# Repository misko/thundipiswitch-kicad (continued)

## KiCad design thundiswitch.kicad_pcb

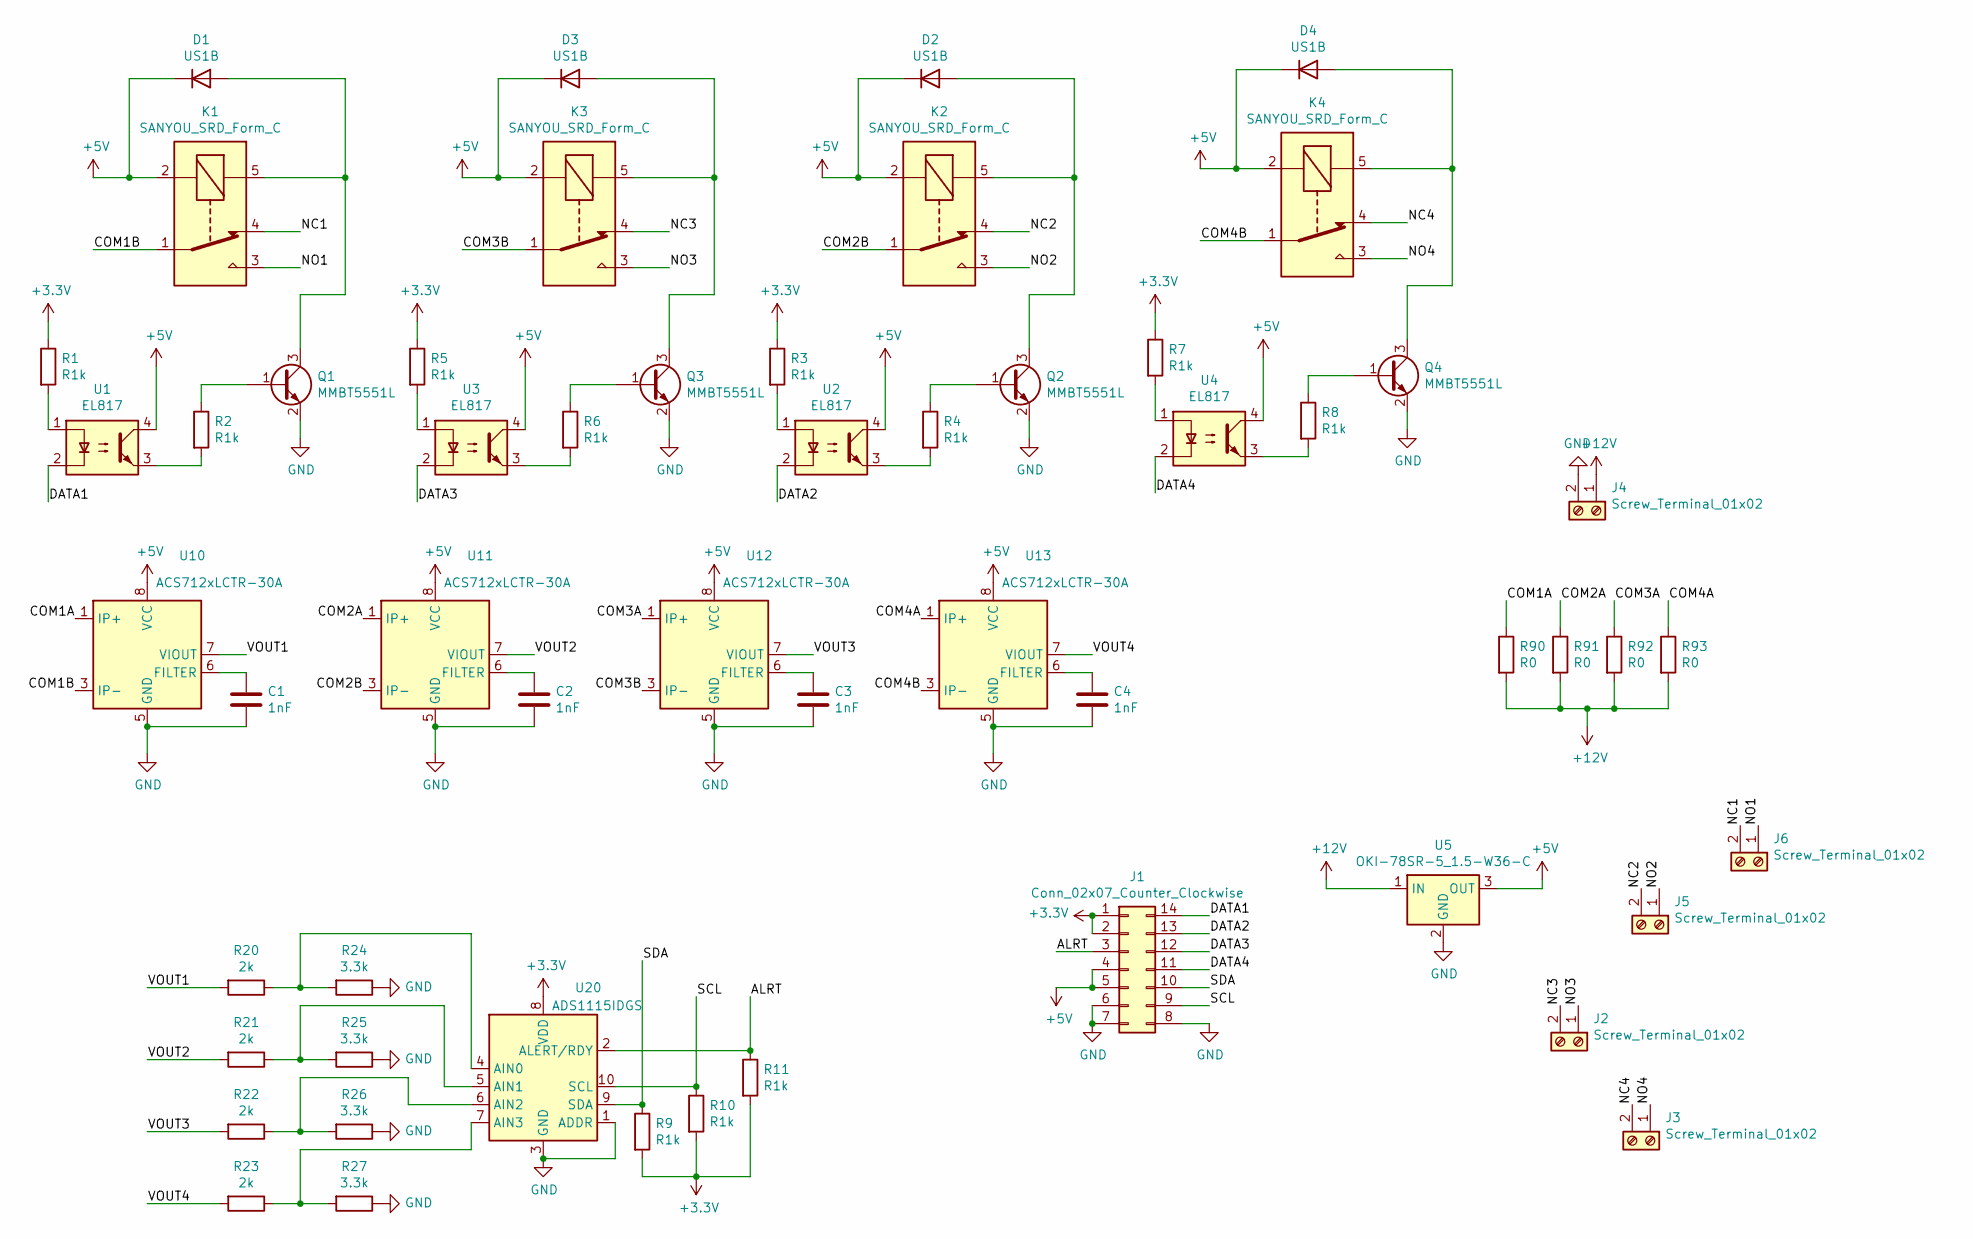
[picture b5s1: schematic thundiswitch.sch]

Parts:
C1, C2, C3, C4: 1nF; C_0603_1608Metric
D1, D2, D3, D4: US1B; D_SMA
J1: Conn_02x07_Counter_Clockwise; PinHeader_2x07_P2.54mm_Vertical
J2, J3, J4, J5, J6: Screw_Terminal_01x02; 1714971
K1, K2, K3, K4: SANYOU_SRD_Form_C; Relay_SPDT_SANYOU_SRD_Series_Form_C
Q1, Q2, Q3, Q4: MMBT5551L; SOT-23
R1, R2, R3, R4, R5, R6, R7, R8, R9, R10, R11: R1k; R_1206_3216Metric
R20, R21, R22, R23: 2k; R_1206_3216Metric
R24, R25, R26, R27: 3.3k; R_1206_3216Metric
R90, R91, R92, R93: R0; R_2512_6332Metric
U1, U2, U3, U4: EL817; SOIC254P1016X385-4N
U5: OKI-78SR-5_1.5-W36-C; Converter_DCDC_muRata_OKI-78SR_Vertical
U10, U11, U12, U13: ACS712xLCTR-30A; SOIC-8_3.9x4.9mm_P1.27mm
U20: ADS1115IDGS; TSSOP-10_3x3mm_P0.5mm

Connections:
+3V3: J1.1, J1.2, R1.1, R3.1, R5.1, R7.1, R9.2, R10.2, R11.2, U20.8 (VDD)
+5V: D1.1 (K), D2.1 (K), D3.1 (K), D4.1 (K), J1.4, J1.5, K1.2, K2.2, K3.2, K4.2, U1.4, U2.4, U3.4, U4.4, U5.3 (OUT), U10.8 (VCC), U11.8 (VCC), U12.8 (VCC), U13.8 (VCC)
+12V: J4.1, R90.2, R91.2, R92.2, R93.2, U5.1 (IN)
/ALRT: J1.3, R11.1, U20.2 (ALERT/RDY)
/COM1A: R90.1, U10.1 (IP+), U10.2 (IP+)
/COM1B: K1.1, U10.3 (IP-), U10.4 (IP-)
/COM2A: R91.1, U11.1 (IP+), U11.2 (IP+)
/COM2B: K2.1, U11.3 (IP-), U11.4 (IP-)
/COM3A: R92.1, U12.1 (IP+), U12.2 (IP+)
/COM3B: K3.1, U12.3 (IP-), U12.4 (IP-)
/COM4A: R93.1, U13.1 (IP+), U13.2 (IP+)
/COM4B: K4.1, U13.3 (IP-), U13.4 (IP-)
/DATA1: J1.14, U1.2
/DATA2: J1.13, U2.2
/DATA3: J1.12, U3.2
/DATA4: J1.11, U4.2
/NC1: J6.2, K1.4
/NC2: J5.2, K2.4
/NC3: J2.2, K3.4
/NC4: J3.2, K4.4
/NO1: J6.1, K1.3
/NO2: J5.1, K2.3
/NO3: J2.1, K3.3
/NO4: J3.1, K4.3
/SCL: J1.9, R10.1, U20.10 (SCL)
/SDA: J1.10, R9.1, U20.9 (SDA)
/VOUT1: R20.2, U10.7 (VIOUT)
/VOUT2: R21.2, U11.7 (VIOUT)
/VOUT3: R22.2, U12.7 (VIOUT)
/VOUT4: R23.2, U13.7 (VIOUT)
GND: C1.2, C2.2, C3.2, C4.2, J1.6, J1.7, J1.8, J4.2, Q1.2 (E), Q2.2 (E), Q3.2 (E), Q4.2 (E), R24.1, R25.1, R26.1, R27.1, U5.2 (GND), U10.5 (GND), U11.5 (GND), U12.5 (GND), U13.5 (GND), U20.1 (ADDR), U20.3 (GND)
unnamed: C1.1, U10.6 (FILTER)
unnamed: C2.1, U11.6 (FILTER)
unnamed: C3.1, U12.6 (FILTER)
unnamed: C4.1, U13.6 (FILTER)
unnamed: D1.2 (A), K1.5, Q1.3 (C)
unnamed: D2.2 (A), K2.5, Q2.3 (C)
unnamed: D3.2 (A), K3.5, Q3.3 (C)
unnamed: D4.2 (A), K4.5, Q4.3 (C)
unnamed: Q1.1 (B), R2.1
unnamed: Q2.1 (B), R4.1
unnamed: Q3.1 (B), R6.1
unnamed: Q4.1 (B), R8.1
unnamed: R1.2, U1.1
unnamed: R2.2, U1.3
unnamed: R3.2, U2.1
unnamed: R4.2, U2.3
unnamed: R5.2, U3.1
unnamed: R6.2, U3.3
unnamed: R7.2, U4.1
unnamed: R8.2, U4.3
unnamed: R20.1, R24.2, U20.4 (AIN0)
unnamed: R21.1, R25.2, U20.5 (AIN1)
unnamed: R22.1, R26.2, U20.6 (AIN2)
unnamed: R23.1, R27.2, U20.7 (AIN3)

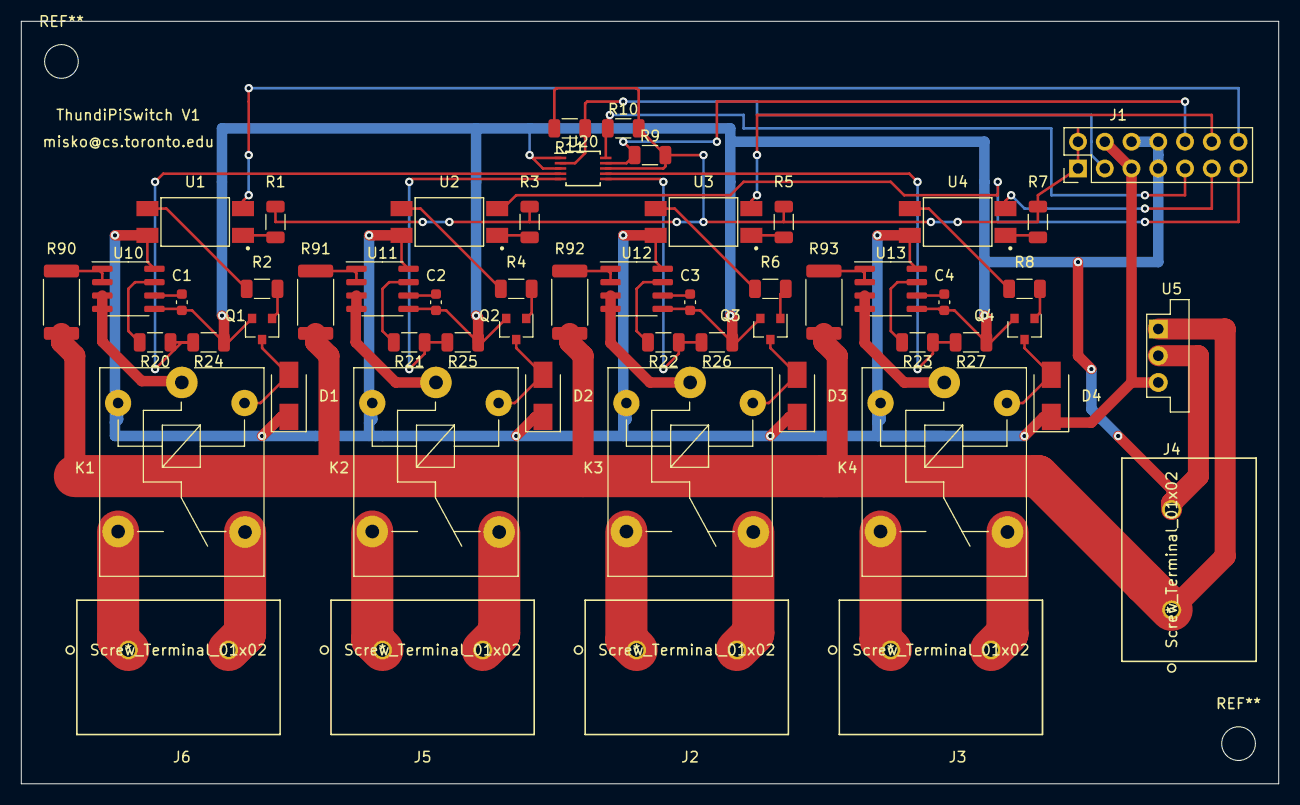
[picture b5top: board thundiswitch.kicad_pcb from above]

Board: 2 copper layers, 119.4 x 72.4 mm, 55 parts (0 on the bottom side), 55 nets.

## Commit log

2021-05-27 updates to board 3.1
2021-07-01 updates before v5
